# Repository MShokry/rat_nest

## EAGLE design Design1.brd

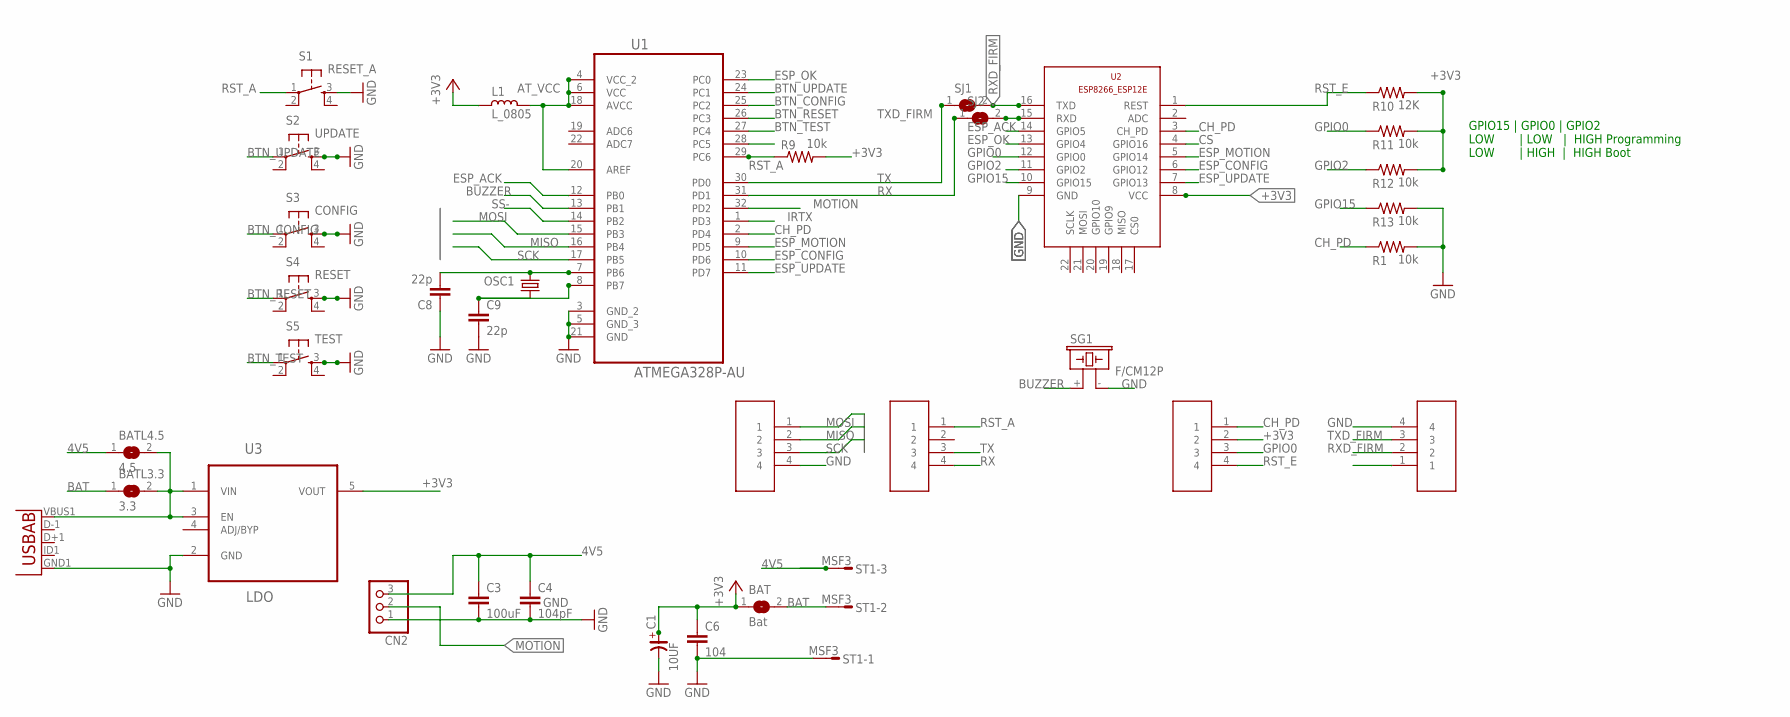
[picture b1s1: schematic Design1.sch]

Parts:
BAT: Bat; SJ
BATL3.3: 3.3; SJ
BATL4.5: 4.5; SJ
C1: 10UF; C6032/T
C3: 100uF; C0805
C4: 104pF; C0805
C6: 104; C0805
C8, C9: 22p; C0805K
CN1: USB""; USB-MICRO-SMD
CN2: PINHD-1X3; 1X03
CON1: AT1; FIRM_PADS
CON2: AT2; FIRM_PADS
CON3: ESP1; FIRM_PADS
CON4: ESP2; FIRM_PADS
L1: L_0805; L0805
OSC1: CRYSTALSM49; SM49
R1, R9, R11, R12, R13: 10k; 0805
R10: 12K; 0805
S1: RESET_A; DTSM-6
S2: UPDATE; DTSM-6
S3: CONFIG; DTSM-6
S4: RESET; DTSM-6
S5: TEST; DTSM-6
SG1: F/CM12P
SJ1, SJ2: SJ
ST1: MSF3
U1: ATMEGA328P-AU; QFP80P900X900X120-32N
U2: ESP8266-12EESP8266-ESP12E; ESP8266-ESP12E
U3: LDO; SOT95P280X145-5N

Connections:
4V5: BATL4.5.1, C3.1, C4.1, CN2.3, ST1.3
+3V3: BAT.1, C1.+, C6.1, CON3.2, L1.2, R9.2, R10.2, R11.2, R12.2, U2.8 (VCC), U3.5 (VOUT)
AT_VCC: L1.1, U1.4 (VCC_2), U1.6 (VCC), U1.18 (AVCC), U1.20 (AREF)
BAT: BAT.2, BATL3.3.1, ST1.2
BTN_CONFIG: S3.1, U1.25 (PC2)
BTN_RESET: S4.1, U1.26 (PC3)
BTN_TEST: S5.1, U1.27 (PC4)
BTN_UPDATE: S2.1, U1.24 (PC1)
BUZZER: SG1.+ (1), U1.13 (PB1)
CH_PD: CON3.1, R1.1, U1.2 (PD4), U2.3 (CH_PD)
CS: U2.4 (GPIO16)
ESP_ACK: U1.12 (PB0), U2.14 (GPIO5)
ESP_CONFIG: U1.10 (PD6), U2.6 (GPIO12)
ESP_MOTION: U1.9 (PD5), U2.5 (GPIO14)
ESP_OK: U1.23 (PC0), U2.13 (GPIO4)
ESP_UPDATE: U1.11 (PD7), U2.7 (GPIO13)
GND: C1.-, C3.2, C4.2, C6.2, C8.1, C9.2, CN1.GND1 (GND), CN2.1, CON1.4, CON4.4, R1.2, R13.2, S1.3, S2.3, S3.3, S4.3, S5.3, SG1.- (2), ST1.1, U1.3 (GND_2), U1.5 (GND_3), U1.21 (GND), U2.9 (GND), U3.2 (GND)
GPIO0: CON3.3, R11.1, U2.12 (GPIO0)
GPIO2: R12.1, U2.11 (GPIO2)
GPIO15: R13.1, U2.10 (GPIO15)
IRTX: U1.1 (PD3)
MISO: CON1.2, U1.16 (PB4)
MOSI: CON1.1, U1.15 (PB3)
MOTION: CN2.2, U1.32 (PD2)
unnamed: BATL3.3.2, BATL4.5.2, CN1.VBUS1 (VBUS), U3.1 (VIN), U3.3 (EN)
unnamed: C8.2, OSC1.1, U1.7 (PB6)
unnamed: C9.1, OSC1.2, U1.8 (PB7)
RST_A: CON2.1, R9.1, S1.1, U1.29 (PC6)
RST_E: CON3.4, R10.1, U2.1 (REST)
RX: CON2.4, SJ2.1, U1.31 (PD1)
RXD_FIRM: CON4.2, SJ1.2, U2.16 (TXD)
SCK: CON1.3, U1.17 (PB5)
SS-: U1.14 (PB2)
TX: CON2.3, SJ1.1, U1.30 (PD0)
TXD_FIRM: CON4.3, SJ2.2, U2.15 (RXD)

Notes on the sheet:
GPIO15 | GPIO0 | GPIO2 LOW | LOW | HIGH Programming LOW | HIGH | HIGH Boot

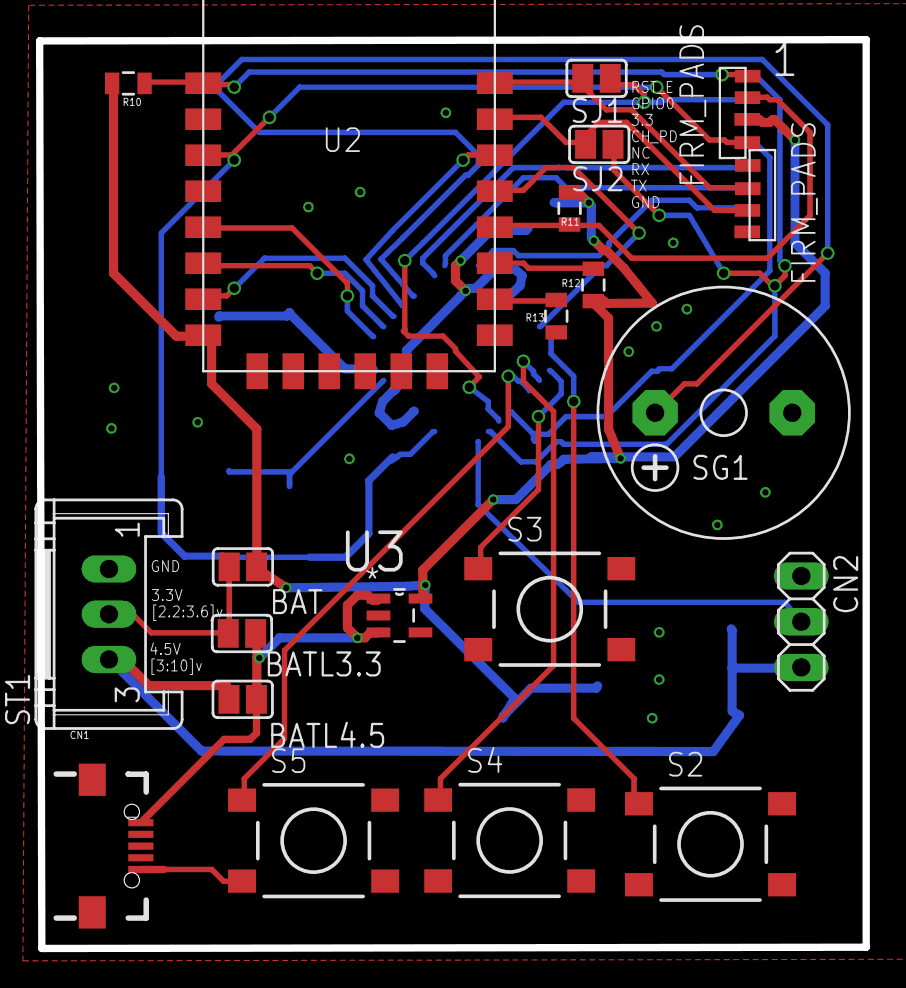
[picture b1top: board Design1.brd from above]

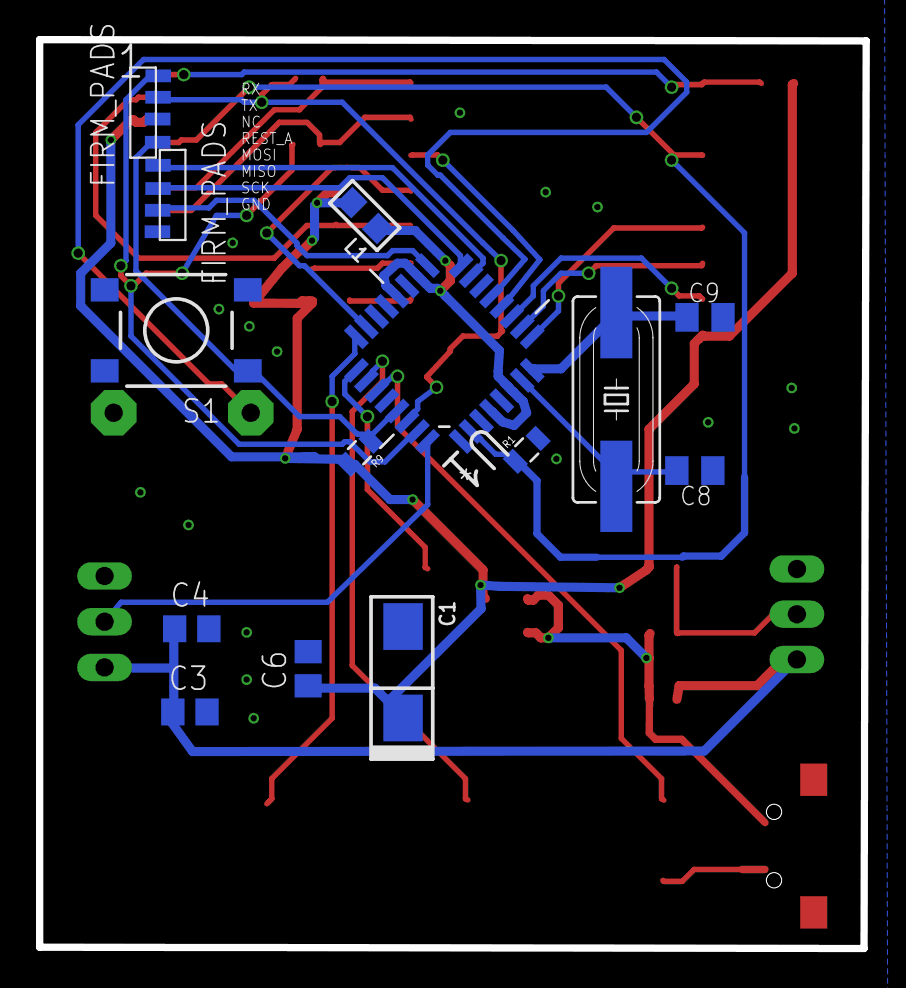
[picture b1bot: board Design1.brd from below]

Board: 2 copper layers, 45.9 x 50.5 mm, 35 parts (14 on the bottom side), 32 nets.

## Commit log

2018-03-27 First Upload
2018-04-01 v 0.3 needs location buttons only
2018-04-02 v 0.5 good
2018-04-06 v0.6
2018-04-17 v 0.6 Add some notes

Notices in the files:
parts and their libraries:
rc-master-smd: Copyright (C) 2007, Bob Starr
SMD Resistors: Licensing: Creative Commons ShareAlike 4.0 International - https://creativecommons.org/licenses/by-sa/4.0
